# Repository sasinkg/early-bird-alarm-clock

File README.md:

# Early Bird Alarm Clock ⏰🚗

An interactive, mobile alarm clock designed to **force users out of bed** by combining physical movement, obstacle avoidance, and cognitive engagement. When the alarm triggers, the clock **drives away from the user** and can only be silenced by solving a math problem.

This project was completed as part of **ECE 445 – Senior Design** (Fall 2022).

---
###  Codebase: https://github.com/siddharthsharma123/ECE445.git
## 🧠 Motivation

Many people rely on repeated alarms and snoozing, which disrupts sleep cycles and reduces morning alertness. The Early Bird Alarm Clock addresses this by:
- Physically forcing the user to get out of bed
- Preventing passive alarm dismissal
- Engaging the user cognitively before silencing the alarm

---

## ✨ Features

- ⏱️ **Fully functional alarm clock**
  - Set current time and alarm time
  - Visual alarm status indicator
- 🚗 **Autonomous movement**
  - Dual DC motors with H-bridge control
  - Obstacle detection via ultrasonic sensors
- 🧮 **Math-based alarm shutdown**
  - Randomly generated arithmetic problem
  - Alarm silences only after correct solution
- 📟 **LCD-based user interface**
  - Clock display
  - Alarm configuration
  - Math problem interaction
- 🔊 **Audible alarm via piezo buzzer**

---

## 🏗️ System Architecture

The system is organized into four primary subsystems:

### 1. UI Module
- 16x2 LCD display
- 8 push buttons (clock control + math input)
- Shift register (74HC165) to reduce I/O pin usage

### 2. Movement Module
- Two 12V DC motors
- L298N dual H-bridge motor driver
- Three HC-SR04 ultrasonic sensors for obstacle avoidance

### 3. Math Module
- Random arithmetic problem generation
- Button-driven numerical input (hundreds / tens / ones)
- Answer verification logic

### 4. Power Module
- Multiple NiMH batteries
- Voltage regulation for logic (5V) and motors (12V)

---

## 🧩 Software Overview

The firmware is written in **C/C++ (Arduino)** and organized modularly:

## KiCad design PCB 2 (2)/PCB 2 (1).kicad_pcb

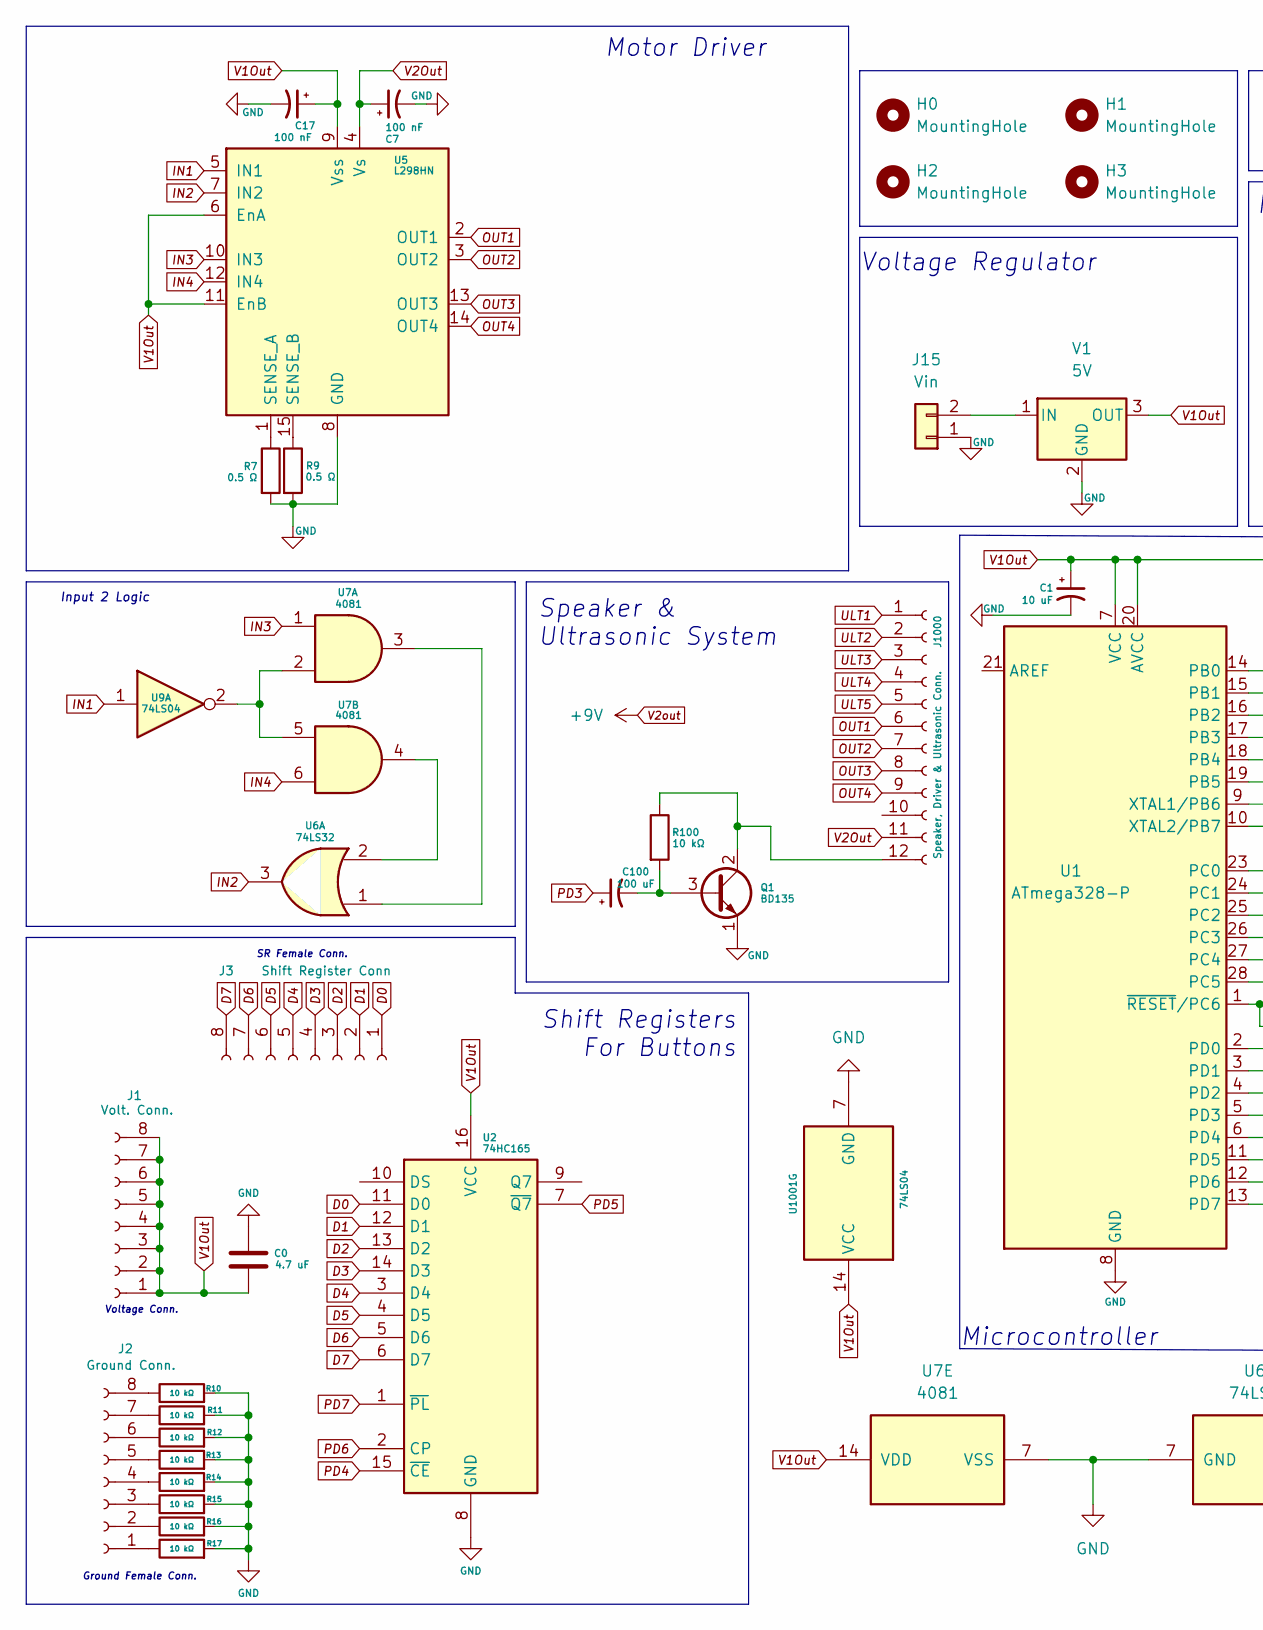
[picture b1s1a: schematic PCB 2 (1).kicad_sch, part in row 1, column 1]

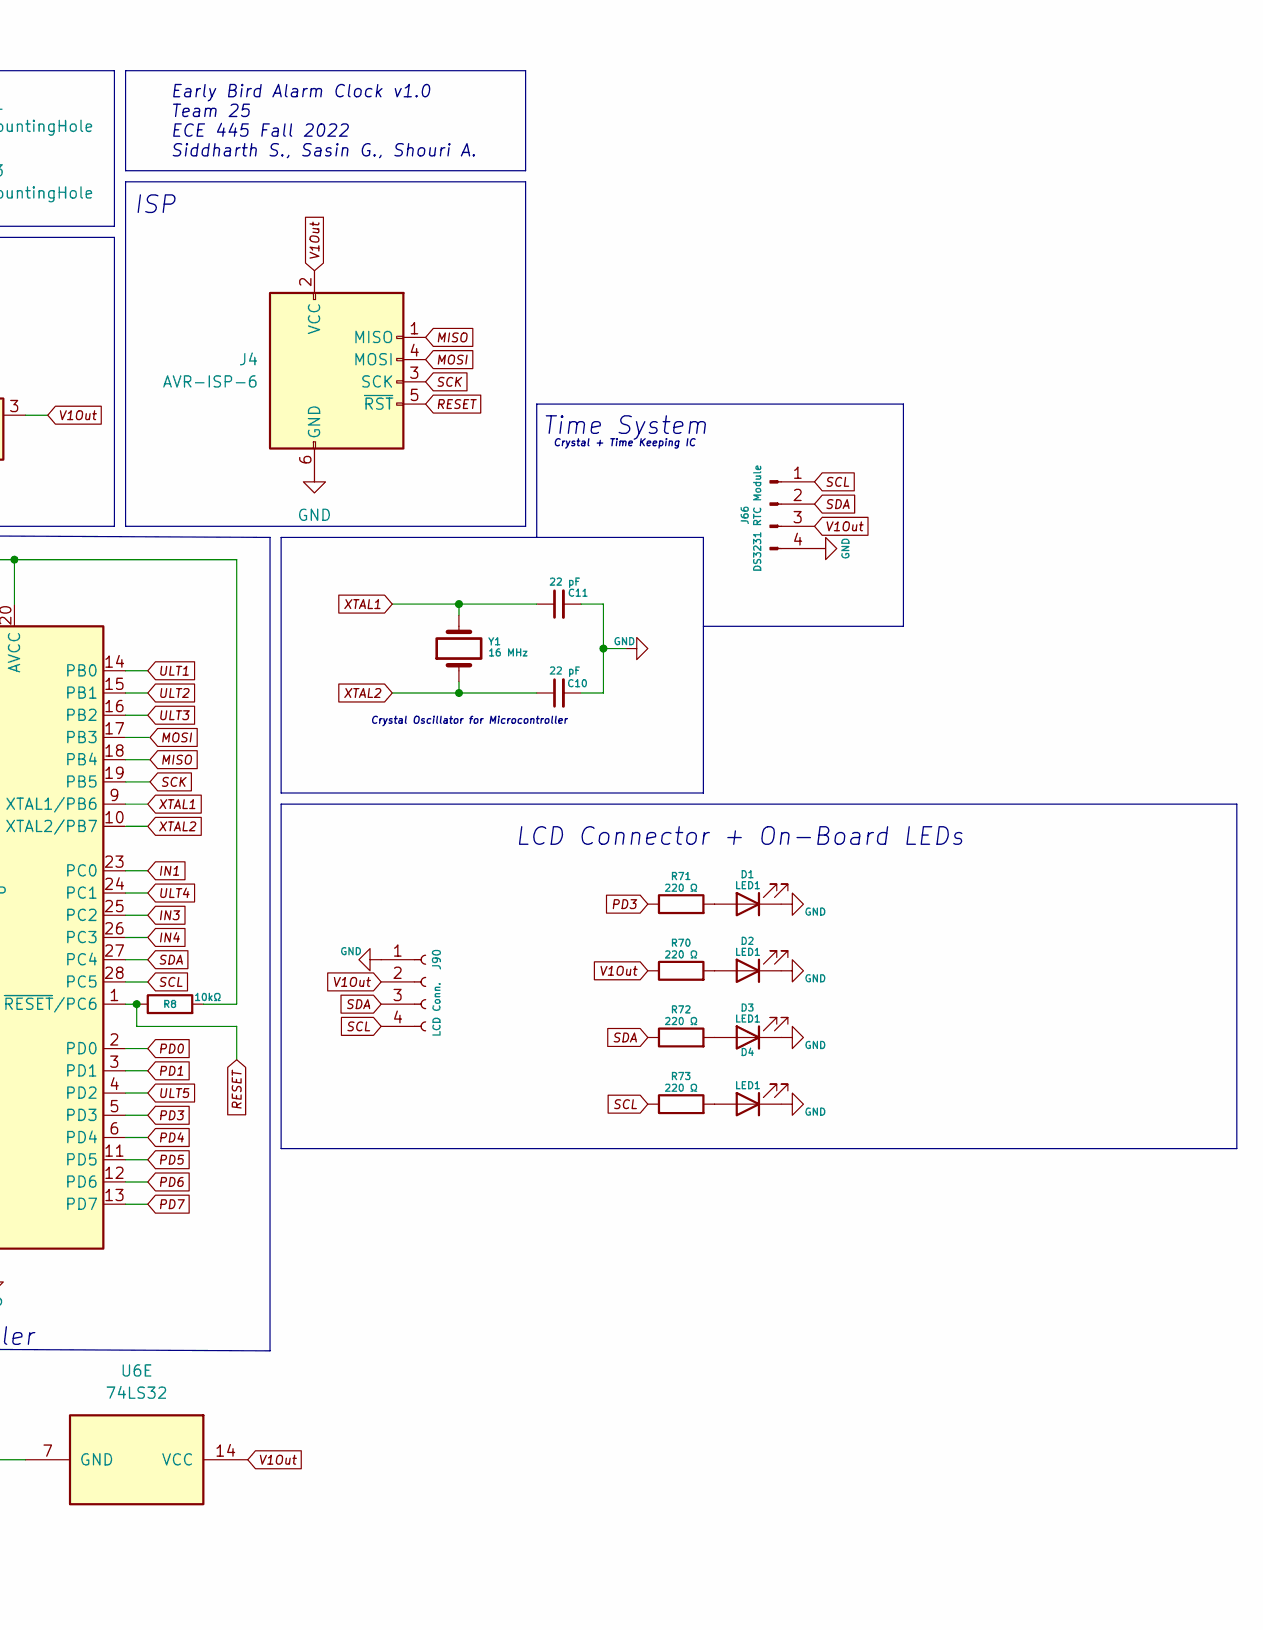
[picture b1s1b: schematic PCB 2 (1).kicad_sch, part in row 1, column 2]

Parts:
C0: 4.7 uF; CP_Elec_3x5.3
C1: 10 uF; CP_Elec_3x5.3
C7, C17: 100 nF; CP_Elec_3x5.3
C10, C11: 22 pF; CP_Elec_3x5.3
C100: 100 uF; CP_Elec_3x5.3
D1, D2, D3, D4: LED1; LED_D1.8mm_W1.8mm_H2.4mm_Horizontal_O1.27mm_Z1.6mm
H0, H1, H2, H3: MountingHole; MountingHole_3.2mm_M3
J1: Volt. Conn.; 61300811821
J2: Ground Conn.; 61300811821
J3: Shift Register Conn; 61300811821
J4: AVR-ISP-6; IDC-Header_2x03_P2.54mm_Vertical
J15: Vin; Molex_CLIK-Mate_502382-0270_1x02-1MP_P1.25mm_Vertical
J66: DS3231 RTC Module; PinSocket_1x04_P2.54mm_Vertical
J90: LCD Conn.; PinHeader_1x04_P2.54mm_Vertical
J1000: Speaker, Driver & Ultrasonic Conn.; PinHeader_1x12_P2.54mm_Vertical
Q1: BD135; TO-126-3_Vertical
R7, R9: 0.5 Ω; R_0805_2012Metric_Pad1.20x1.40mm_HandSolder
R8: 10kΩ; R_0805_2012Metric_Pad1.20x1.40mm_HandSolder
R10, R11, R12, R13, R14, R15, R16, R17, R100: 10 kΩ; R_0805_2012Metric_Pad1.20x1.40mm_HandSolder
R70, R71, R72, R73: 220 Ω; R_0805_2012Metric_Pad1.20x1.40mm_HandSolder
U1: ATmega328-P; DIP-28_W7.62mm
U2: 74HC165; SO-16
U5: L298HN; TO-220-15_P2.54x2.54mm_StaggerOdd_Lead5.84mm_TabDown
U6: 74LS32; DIP794W45P254L1969H508Q14
U7: 4081; DIP794W45P254L1969H508Q14
U9, U1001: 74LS04; DIP794W46P254L1969H533Q14
V1: 5V; TO254P1054X470X2600-3
Y1: 16 MHz; XTAL_HC49P488W46L1150T500H350

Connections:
D0: J3.1, U2.11 (D0)
D1: J3.2, U2.12 (D1)
D2: J3.3, U2.13 (D2)
D3: J3.4, U2.14 (D3)
D4: J3.5, U2.3 (D4)
D5: J3.6, U2.4 (D5)
D6: J3.7, U2.5 (D6)
D7: J3.8, U2.6 (D7)
GND: C0.1, C1.2, C7.2, C10.2, C11.2, C17.2, D1.1 (K), D2.1 (K), D3.1 (K), D4.1 (K), J4.6 (GND), J15.1, J66.4, J90.1, Q1.1 (E), R7.2, R9.2, R10.2, R11.2, R12.2, R13.2, R14.2, R15.2, R16.2, R17.2, U1.8 (GND), U1.22 (GND), U2.8 (GND), U5.8 (GND), U6.7 (GND), U7.7 (VSS), U1001.7 (GND), V1.2 (GND)
IN1: U1.23 (PC0), U5.5 (IN1), U9.1
IN2: U5.7 (IN2), U6.3
IN3: U1.25 (PC2), U5.10 (IN3), U7.1
IN4: U1.26 (PC3), U5.12 (IN4), U7.6
MISO: J4.1 (MISO), U1.18 (PB4)
MOSI: J4.4 (MOSI), U1.17 (PB3)
unnamed: C100.2, Q1.3 (B), R100.2
unnamed: D1.2 (A), R71.2
unnamed: D2.2 (A), R70.2
unnamed: D3.2 (A), R72.2
unnamed: D4.2 (A), R73.2
unnamed: J2.1, R17.1
unnamed: J2.2, R16.1
unnamed: J2.3, R15.1
unnamed: J2.4, R14.1
unnamed: J2.5, R13.1
unnamed: J2.6, R12.1
unnamed: J2.7, R11.1
unnamed: J2.8, R10.1
unnamed: J15.2, V1.1 (IN)
unnamed: J1000.12, Q1.2 (C), R100.1
unnamed: R7.1, U5.1 (SENSE_A)
unnamed: R9.1, U5.15 (SENSE_B)
unnamed: U6.1, U7.3
unnamed: U6.2, U7.4
unnamed: U7.2, U7.5, U9.2
OUT1: J1000.6, U5.2 (OUT1)
OUT2: J1000.7, U5.3 (OUT2)
OUT3: J1000.8, U5.13 (OUT3)
OUT4: J1000.9, U5.14 (OUT4)
PD0: U1.2 (PD0)
PD1: U1.3 (PD1)
PD3: C100.1, R71.1, U1.5 (PD3)
PD4: U1.6 (PD4), U2.15 (~CE)
PD5: U1.11 (PD5), U2.7 (~Q7)
PD6: U1.12 (PD6), U2.2 (CP)
PD7: U1.13 (PD7), U2.1 (~PL)
RESET: J4.5 (~RST), R8.1, U1.1 (~RESET/PC6)
SCK: J4.3 (SCK), U1.19 (PB5)
SCL: J66.1, J90.4, R73.1, U1.28 (PC5)
SDA: J66.2, J90.3, R72.1, U1.27 (PC4)
ULT1: J1000.1, U1.14 (PB0)
ULT2: J1000.2, U1.15 (PB1)
ULT3: J1000.3, U1.16 (PB2)
ULT4: J1000.4, U1.24 (PC1)
ULT5: J1000.5, U1.4 (PD2)
V1Out: C0.2, C1.1, C17.1, J1.1, J1.2, J1.3, J1.4, J1.5, J1.6, J1.7, J1.8, J4.2 (VCC), J66.3, J90.2, R8.2, R70.1, U1.7 (VCC), U1.20 (AVCC), U2.16 (VCC), U5.6 (EnA), U5.9 (Vss), U5.11 (EnB), U6.14 (VCC), U7.14 (VDD), U1001.14 (VCC), V1.3 (OUT)
V2Out: C7.1, J1000.11, U5.4 (Vs)
XTAL1: C11.1, U1.9 (XTAL1/PB6), Y1.2
XTAL2: C10.1, U1.10 (XTAL2/PB7), Y1.1

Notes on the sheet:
Shift Registers For Buttons
Crystal Oscillator for Microcontroller
LCD Connector + On-Board LEDs
Voltage Regulator
ISP
Crystal + Time Keeping IC
Speaker & Ultrasonic System
Input 2 Logic
Time System
Voltage Conn.
SR Female Conn.
Microcontroller
Motor Driver
Early Bird Alarm Clock v1.0 Team 25 ECE 445 Fall 2022 Siddharth S., Sasin G., Shouri A.
Ground Female Conn.

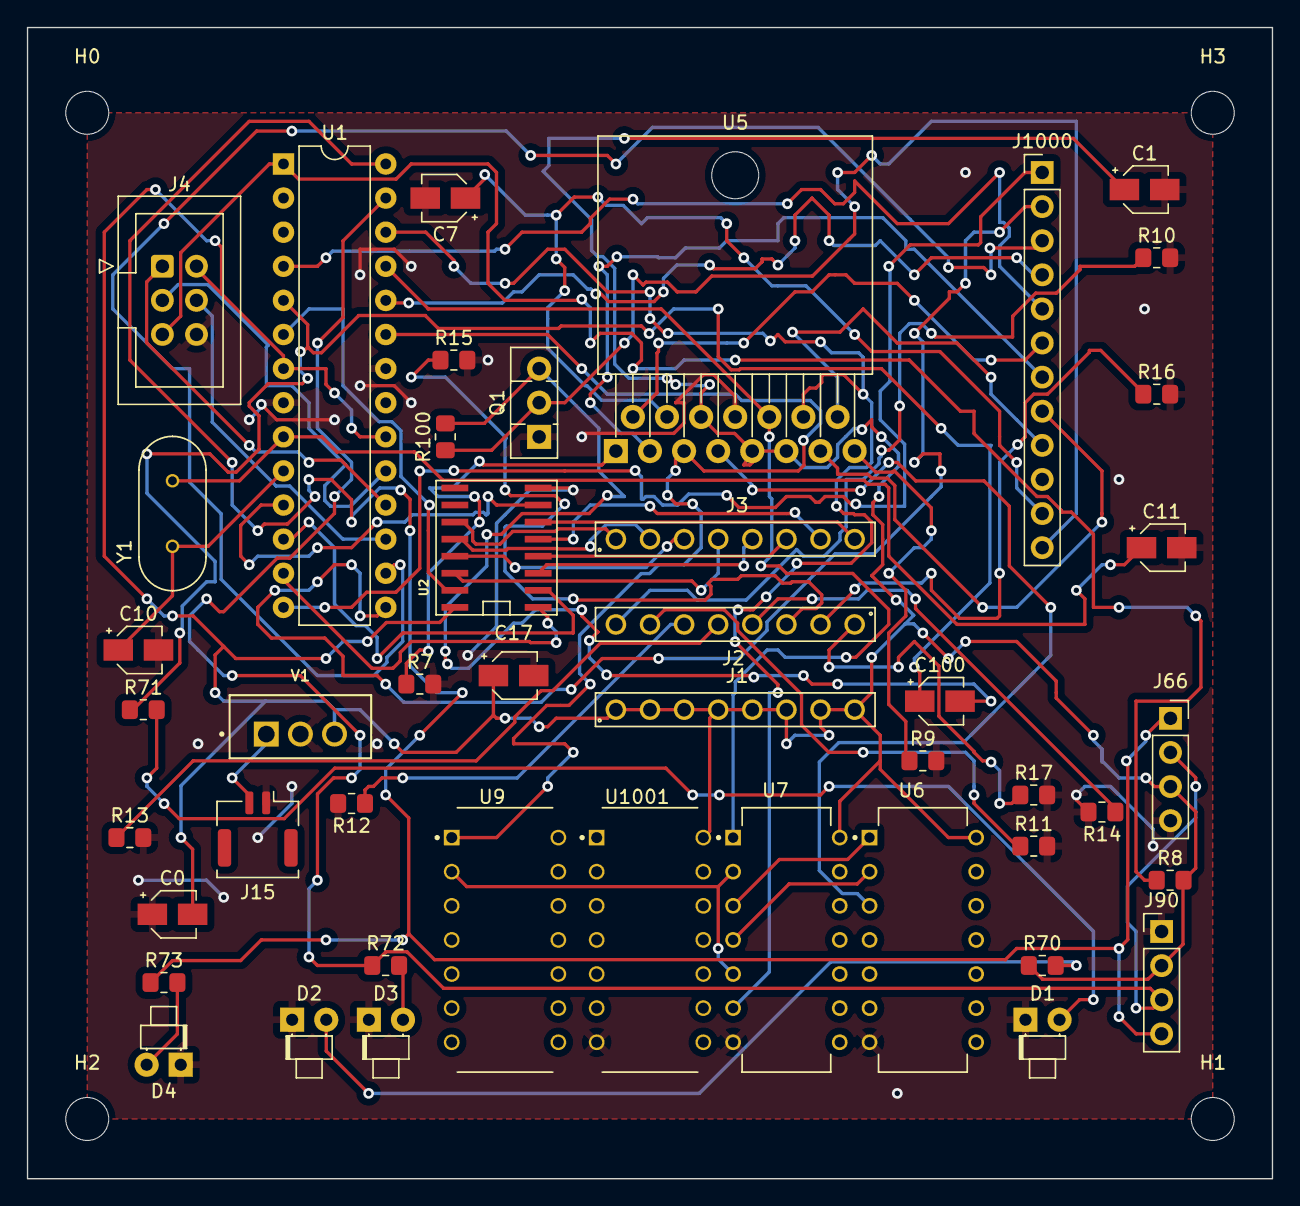
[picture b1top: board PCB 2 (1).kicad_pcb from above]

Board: 2 copper layers, 92.7 x 85.7 mm, 49 parts (0 on the bottom side), 57 nets.

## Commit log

2026-01-30 Uploading PCB Design
2026-01-30 Update codebase link format in README
2026-01-30 Fix codebase link formatting in README
    Updated the codebase link format in the README.
